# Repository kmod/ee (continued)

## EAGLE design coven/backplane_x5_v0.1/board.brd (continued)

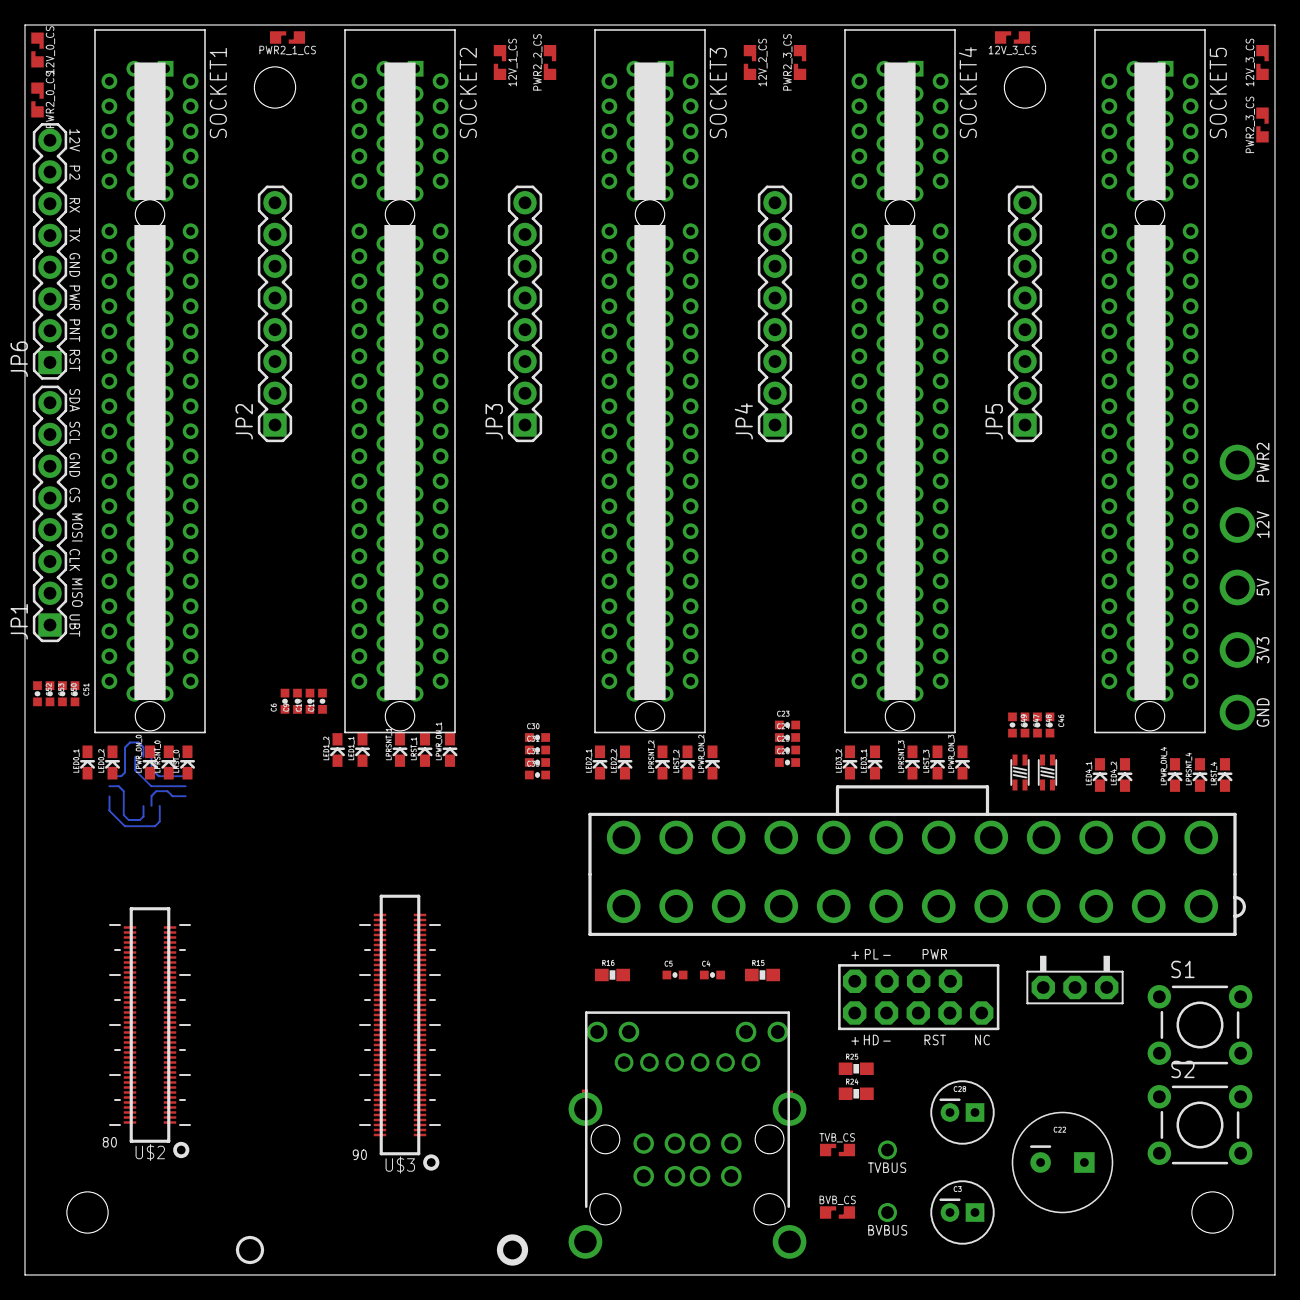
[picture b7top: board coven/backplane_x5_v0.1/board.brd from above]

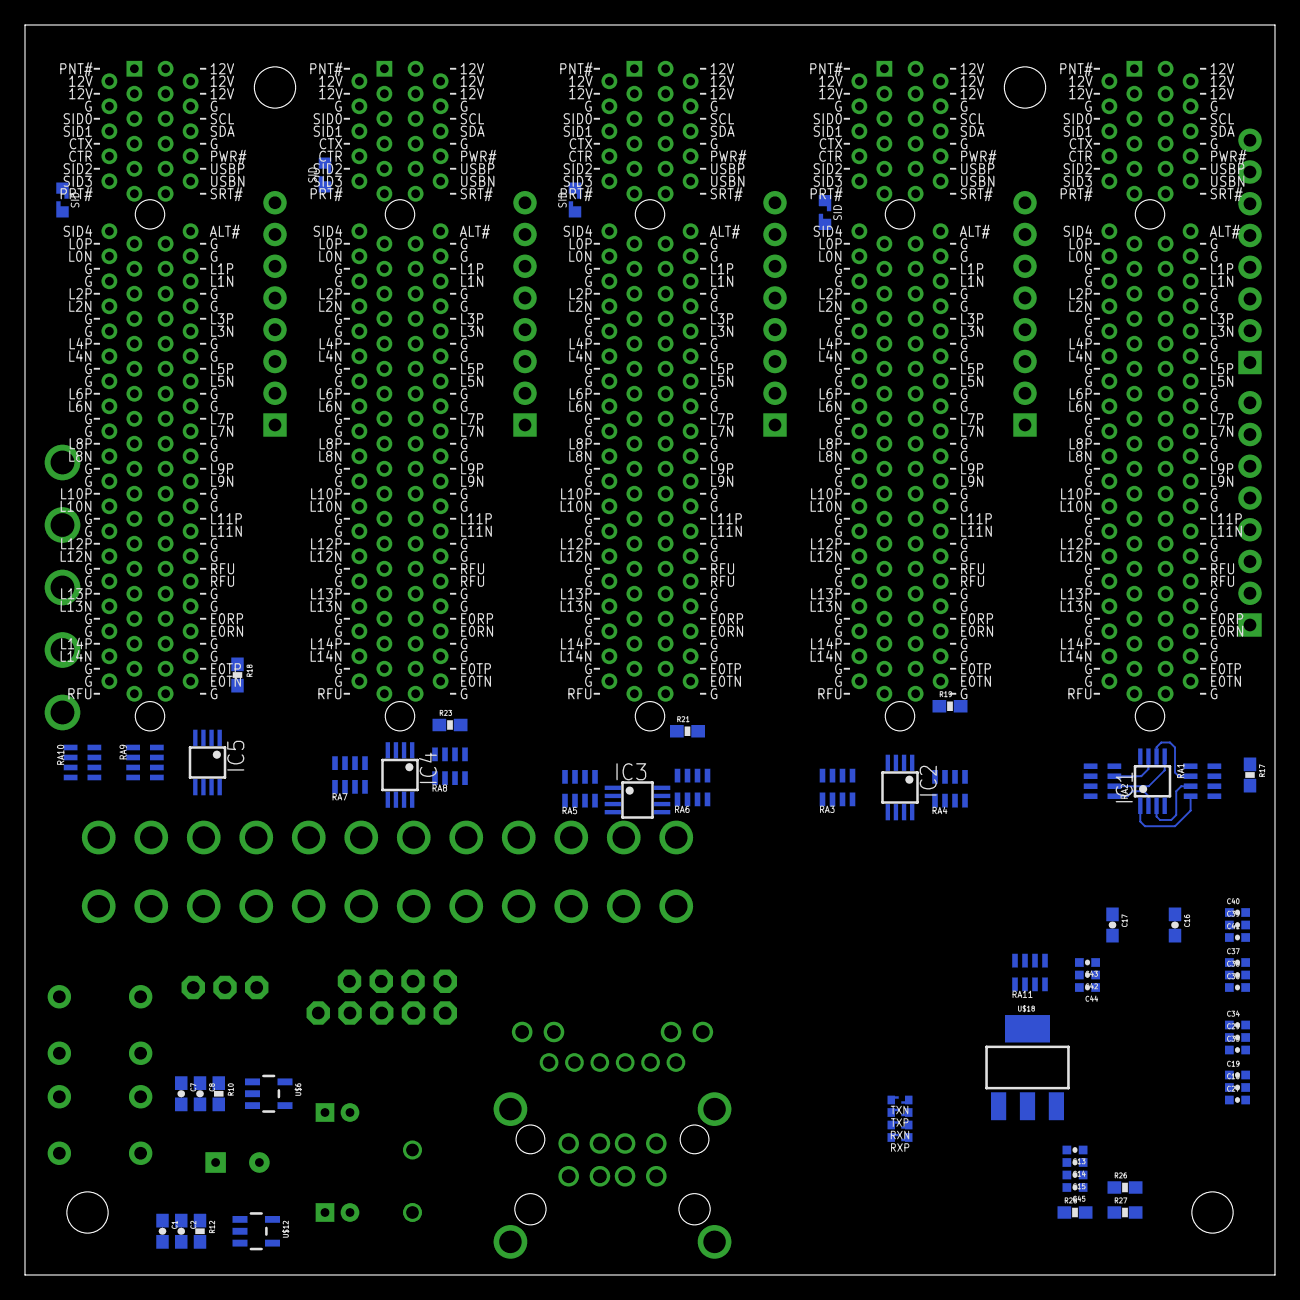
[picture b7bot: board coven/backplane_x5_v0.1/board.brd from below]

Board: 4 copper layers, 100.0 x 100.0 mm, 160 parts (62 on the bottom side), 206 nets.

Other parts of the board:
U$7, U$8, U$9, U$10: STAND-OFF

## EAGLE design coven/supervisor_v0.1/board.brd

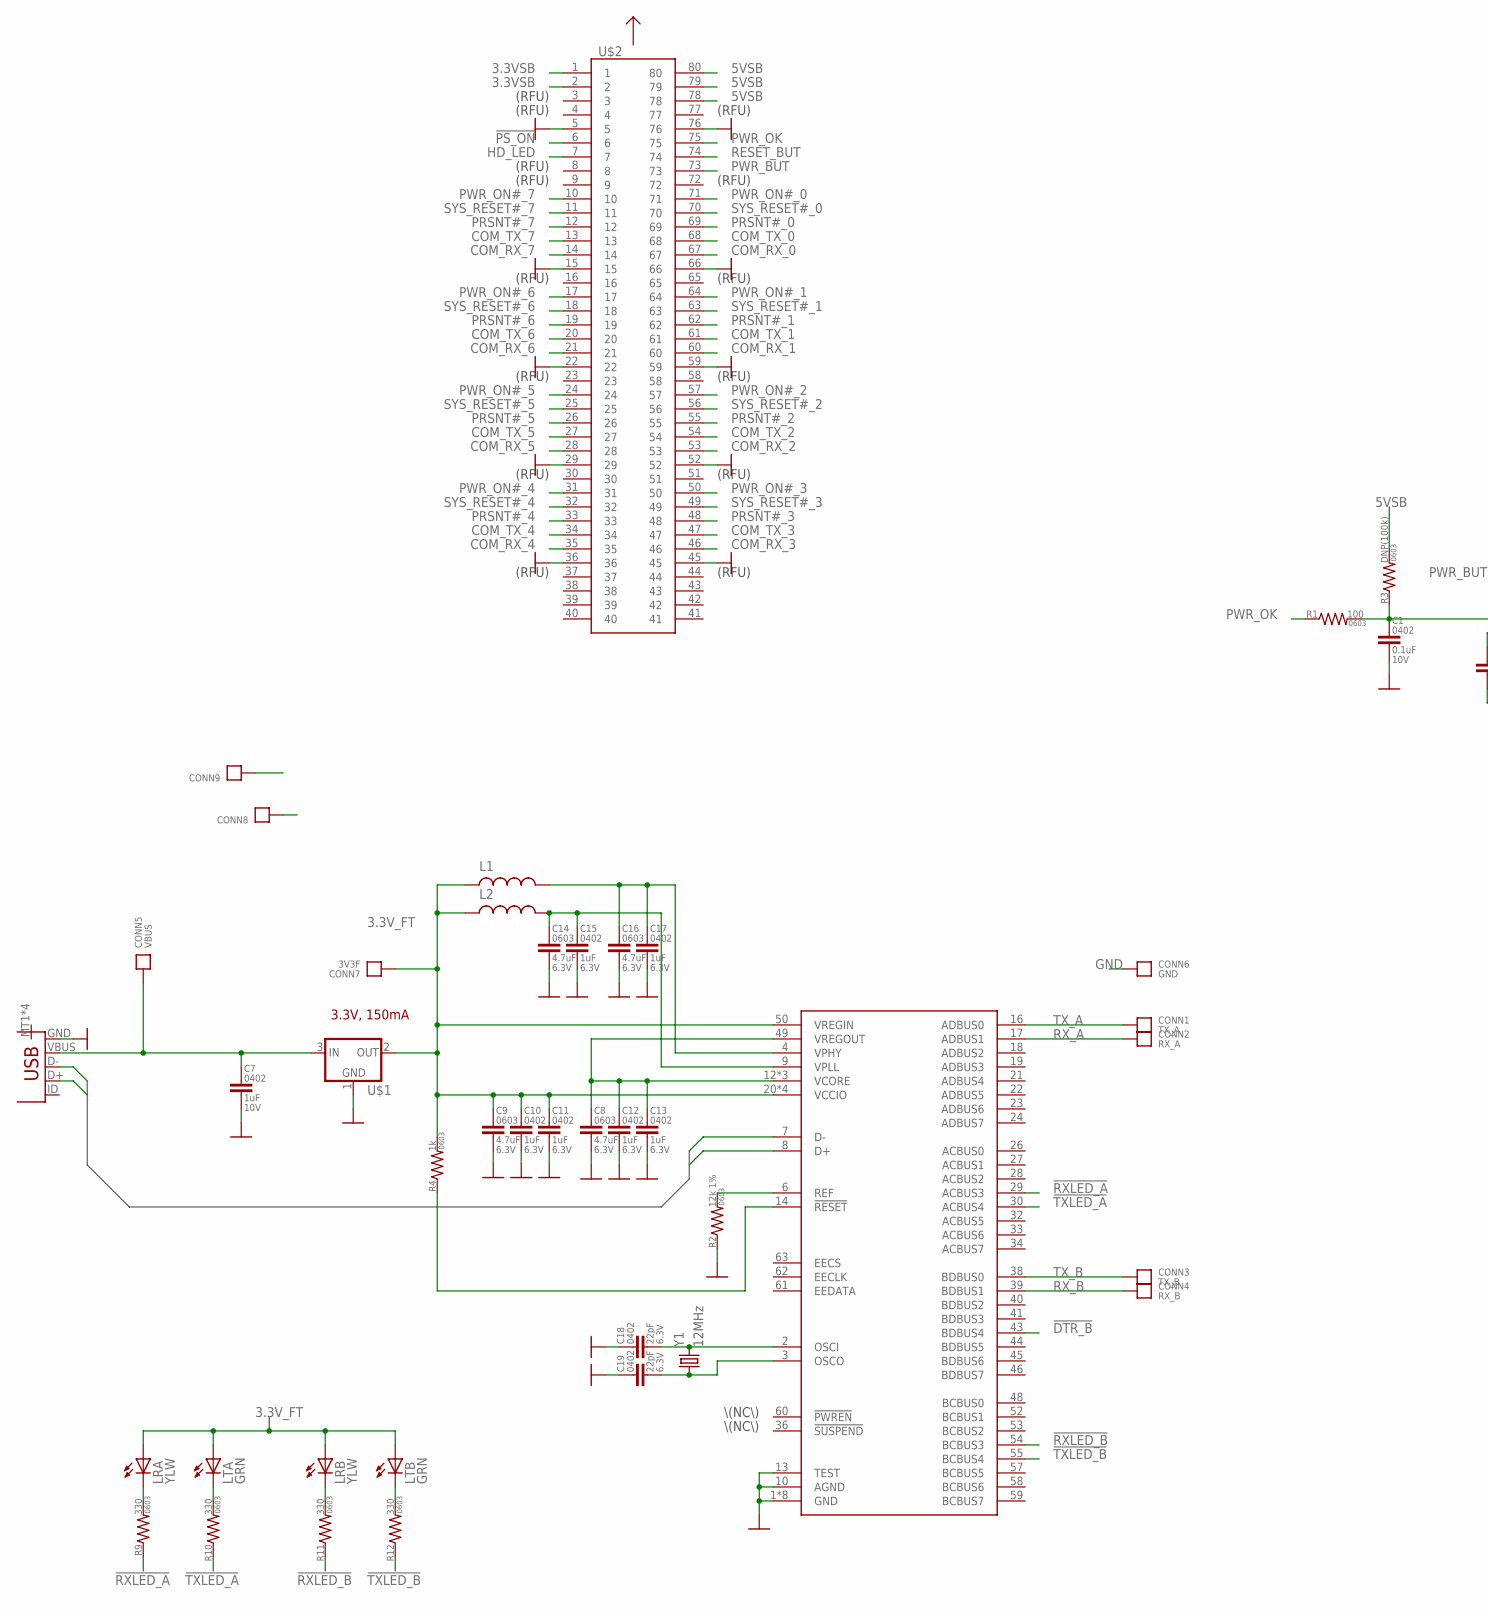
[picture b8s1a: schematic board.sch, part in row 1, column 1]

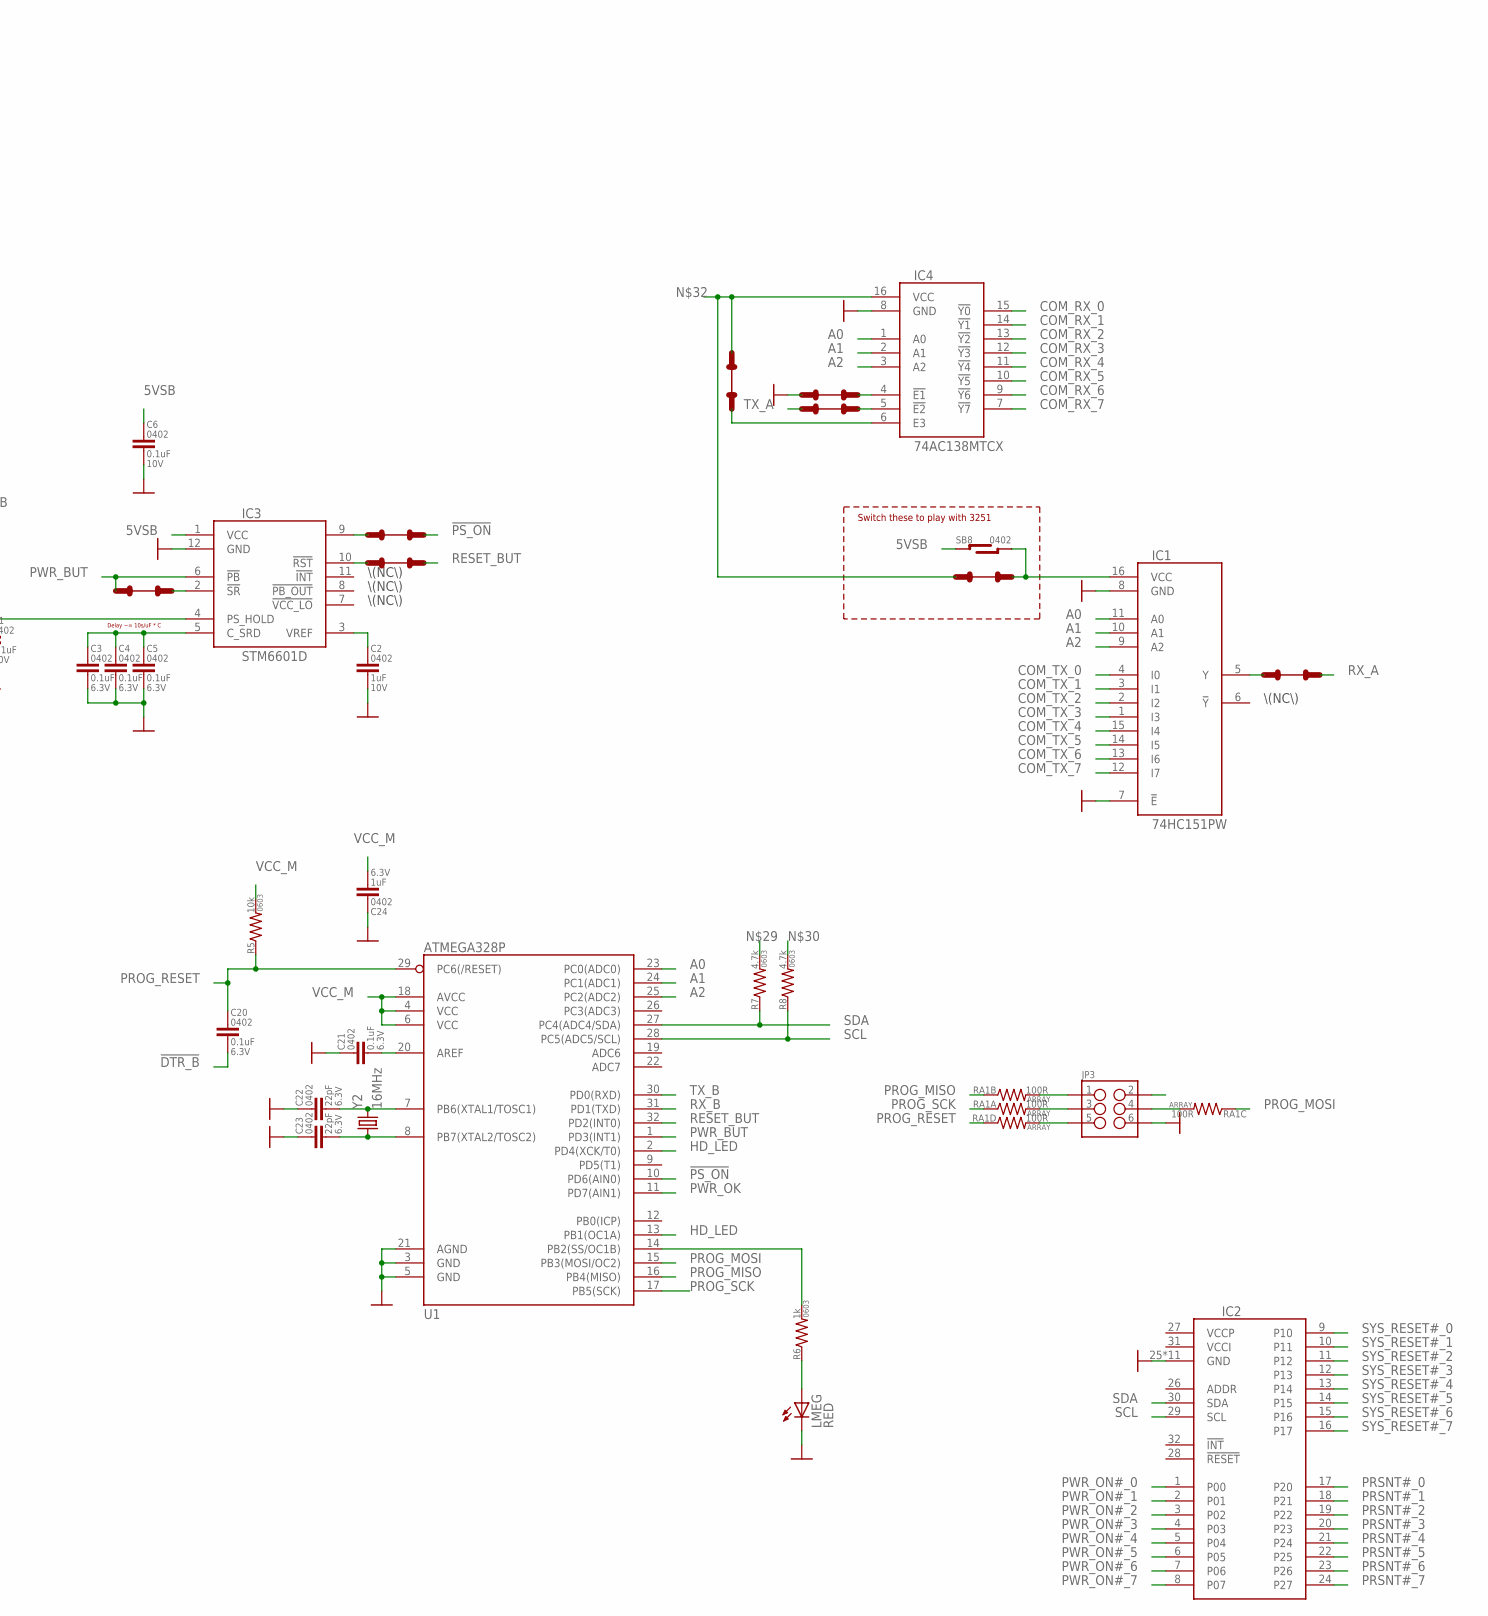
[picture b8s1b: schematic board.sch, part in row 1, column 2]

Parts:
C1, C6: 0.1uF; 0402-CAP; VOLTAGE 10V
C2, C7: 1uF; 0402-CAP; VOLTAGE 10V
C3, C4, C5, C20, C21: 0.1uF; 0402-CAP
C8, C9, C14, C16: 4.7uF; 0603-CAP
C10, C11, C12, C13, C15, C17, C24: 1uF; 0402-CAP
C18, C19, C22, C23: 22pF; 0402-CAP
CONN1: TX_A; HOLE_22AWG
CONN2: RX_A; HOLE_22AWG
CONN3: TX_B; HOLE_22AWG
CONN4: RX_B; HOLE_22AWG
CONN5: VBUS; HOLE_22AWG
CONN6: GND; HOLE_22AWG
CONN7: 3V3F; HOLE_22AWG
CONN8, CONN9: CONNECTOR22AWG; HOLE_22AWG
IC1: 74HC151PW; TSSOP16
IC2: TCA6424A; QFN32
IC3: STM6601D; TDFN12
IC4: 74AC138MTCX; TSSOP16
IC5: FT2232HL; TQFP64_LONGPAD
JP1: USB-IDMICRO; USB-MICRO
JP3: M03X2; 2X3_SMD
L1, L2: INDUCTOR0603; 0603
LMEG: RED; 0603_LED
LRA: YLW; 0603_LED
LRB: YLW; 0603_LED
LTA: GRN; 0603_LED
LTB: GRN; 0603_LED
R1: 100; 0603-RES
R2: 12k 1%; 0603-RES
R3: DNP(100k); 0603-RES
R4, R6: 1k; 0603-RES
R5: 10k; 0603-RES
R7, R8: 4.7k; 0603-RES
R9, R10, R11, R12: 330; 0603-RES
RA1: 100R; 0603-ARV
SB1, SB2, SB3, SB4, SB5, SB6, SB7, SB9: TRACE-CUT
SB8: SOLDER-BRIDGE0402; SB-0402
U1: ATMEGA328P; TQFP32-08
U$1: VREGSOT23-3; SOT23-3
U$2: DF40-80HDR; DF40-HDR-80
Y1: 12MHz; HC49UP
Y2: 16MHz; HC49UP

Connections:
3.3VSB: U$2.1, U$2.2
3.3V_FT: C9.1, C10.1, C11.1, CONN7.P, IC5.20 (VCCIO), IC5.31 (VCCIO), IC5.42 (VCCIO), IC5.50 (VREGIN), IC5.56 (VCCIO), L1.1, L2.1, LRA.A, LRB.A, LTA.A, LTB.A, R4.2, U$1.2 (OUT)
5VSB: C6.1, IC3.1 (VCC), R3.2, SB8.L1, SB8.L2, U$2.78, U$2.79, U$2.80
!DTR_B: C20.2, IC5.43 (BDBUS4)
!PS_ON: SB1.R1, U1.10 (PD6(AIN0)), U$2.6
!RXLED_A: IC5.29 (ACBUS3), R9.1
!RXLED_B: IC5.54 (BCBUS3), R11.1
!TXLED_A: IC5.30 (ACBUS4), R10.1
!TXLED_B: IC5.55 (BCBUS4), R12.1
A0: IC1.11 (A0), IC4.1 (A0), U1.23 (PC0(ADC0))
A1: IC1.10 (A1), IC4.2 (A1), U1.24 (PC1(ADC1))
A2: IC1.9 (A2), IC4.3 (A2), U1.25 (PC2(ADC2))
COM_RX_0: IC4.15 (!Y0), U$2.67
COM_RX_1: IC4.14 (!Y1), U$2.60
COM_RX_2: IC4.13 (!Y2), U$2.53
COM_RX_3: IC4.12 (!Y3), U$2.46
COM_RX_4: IC4.11 (!Y4), U$2.35
COM_RX_5: IC4.10 (!Y5), U$2.28
COM_RX_6: IC4.9 (!Y6), U$2.21
COM_RX_7: IC4.7 (!Y7), U$2.14
COM_TX_0: IC1.4 (I0), U$2.68
COM_TX_1: IC1.3 (I1), U$2.61
COM_TX_2: IC1.2 (I2), U$2.54
COM_TX_3: IC1.1 (I3), U$2.47
COM_TX_4: IC1.15 (I4), U$2.34
COM_TX_5: IC1.14 (I5), U$2.27
COM_TX_6: IC1.13 (I6), U$2.20
COM_TX_7: IC1.12 (I7), U$2.13
D+: IC5.8 (D+), JP1.D+
D-: IC5.7 (D-), JP1.D-
GND: C1.2, C2.2, C3.2, C4.2, C5.2, C6.2, C7.2, C8.2, C9.2, C10.2, C11.2, C12.2, C13.2, C14.2, C15.2, C16.2, C17.2, C18.1, C19.1, C21.1, C22.1, C23.1, C24.1, CONN6.P, IC1.7 (!E), IC1.8 (GND), IC2.25 (GND), IC2.PAD (GND), IC2.PAD1 (GND), IC2.PAD2 (GND), IC2.PAD3 (GND), IC2.PAD4 (GND), IC2.PAD5 (GND), IC2.PAD6 (GND), IC2.PAD7 (GND), IC2.PAD8 (GND), IC2.PAD9 (GND), IC3.12 (GND), IC4.8 (GND), IC5.1 (GND), IC5.5 (GND), IC5.10 (AGND), IC5.11 (GND), IC5.13 (TEST), IC5.15 (GND), IC5.25 (GND), IC5.35 (GND), IC5.47 (GND), IC5.51 (GND), JP1.GND, JP3.6, LMEG.C, R2.1, SB4.L1, U1.3 (GND), U1.5 (GND), U1.21 (AGND), U$1.1 (GND), U$2.5, U$2.15, U$2.22, U$2.29, U$2.36, U$2.45, U$2.52, U$2.59, U$2.66, U$2.76
HD_LED: U1.2 (PD4(XCK/T0)), U1.13 (PB1(OC1A)), U$2.7
unnamed: IC3.10 (!RST), SB3.L1
unnamed: C1.1, IC3.4 (PS_HOLD), R1.2, R3.1
unnamed: IC3.9 (EN/!EN), SB1.L1
unnamed: C2.1, IC3.3 (VREF)
unnamed: C3.1, C4.1, C5.1, IC3.5 (C_SRD)
unnamed: IC3.2 (!SR), SB2.R1
unnamed: C7.1, CONN5.P, JP1.VBUS, U$1.3 (IN)
unnamed: C14.1, C15.1, IC5.9 (VPLL), L2.2
unnamed: IC5.6 (REF), R2.2
unnamed: C8.1, C12.1, C13.1, IC5.12 (VCORE), IC5.37 (VCORE), IC5.49 (VREGOUT), IC5.64 (VCORE)
unnamed: C16.1, C17.1, IC5.4 (VPHY), L1.2
unnamed: IC5.14 (!RESET), R4.1
unnamed: C18.2, IC5.2 (OSCI), Y1.2
unnamed: C19.2, IC5.3 (OSCO), Y1.1
unnamed: C21.2, U1.20 (AREF)
unnamed: LRA.C, R9.2
unnamed: LTA.C, R10.2
unnamed: LRB.C, R11.2
unnamed: LTB.C, R12.2
unnamed: C22.2, U1.7 (PB6(XTAL1/TOSC1)), Y2.2
unnamed: C23.2, U1.8 (PB7(XTAL2/TOSC2)), Y2.1
unnamed: JP3.4, RA1.6 (2)
unnamed: IC4.6 (E3), SB5.L1
unnamed: JP3.5, RA1.5 (2)
unnamed: JP3.3, RA1.8 (2)
unnamed: JP3.1, RA1.7 (2)
unnamed: IC4.4 (!E1), SB4.R1
unnamed: IC4.16 (VCC), SB5.R1, SB9.L1
unnamed: IC4.5 (!E2), SB6.R1
unnamed: IC1.5 (Y), SB7.L1
unnamed: R6.2, U1.14 (PB2(SS/OC1B))
unnamed: LMEG.A, R6.1
unnamed: IC1.16 (VCC), SB8.R1, SB8.R2, SB9.R1
PROG_MISO: RA1.2 (1), U1.16 (PB4(MISO))
PROG_MOSI: RA1.3 (1), U1.15 (PB3(MOSI/OC2))
PROG_RESET: C20.1, R5.1, RA1.4 (1), U1.29 (PC6(/RESET))
PROG_SCK: RA1.1, U1.17 (PB5(SCK))
PRSNT#_0: IC2.17 (P20), U$2.69
PRSNT#_1: IC2.18 (P21), U$2.62
PRSNT#_2: IC2.19 (P22), U$2.55
PRSNT#_3: IC2.20 (P23), U$2.48
PRSNT#_4: IC2.21 (P24), U$2.33
PRSNT#_5: IC2.22 (P25), U$2.26
PRSNT#_6: IC2.23 (P26), U$2.19
PRSNT#_7: IC2.24 (P27), U$2.12
PWR_BUT: IC3.6 (!PB), SB2.L1, U1.1 (PD3(INT1)), U$2.73
PWR_OK: R1.1, U1.11 (PD7(AIN1)), U$2.75
PWR_ON#_0: IC2.1 (P00), U$2.71
PWR_ON#_1: IC2.2 (P01), U$2.64
PWR_ON#_2: IC2.3 (P02), U$2.57
PWR_ON#_3: IC2.4 (P03), U$2.50
PWR_ON#_4: IC2.5 (P04), U$2.31
PWR_ON#_5: IC2.6 (P05), U$2.24
PWR_ON#_6: IC2.7 (P06), U$2.17
PWR_ON#_7: IC2.8 (P07), U$2.10
RESET_BUT: SB3.R1, U1.32 (PD2(INT0)), U$2.74
RX_A: CONN2.P, IC5.17 (ADBUS1), SB7.R1
RX_B: CONN4.P, IC5.39 (BDBUS1), U1.31 (PD1(TXD))
SCL: IC2.29 (SCL), R8.1, U1.28 (PC5(ADC5/SCL))
SDA: IC2.30 (SDA), R7.1, U1.27 (PC4(ADC4/SDA))
SYS_RESET#_0: IC2.9 (P10), U$2.70
SYS_RESET#_1: IC2.10 (P11), U$2.63
SYS_RESET#_2: IC2.11 (P12), U$2.56
SYS_RESET#_3: IC2.12 (P13), U$2.49
SYS_RESET#_4: IC2.13 (P14), U$2.32
SYS_RESET#_5: IC2.14 (P15), U$2.25
SYS_RESET#_6: IC2.15 (P16), U$2.18
SYS_RESET#_7: IC2.16 (P17), U$2.11
TX_A: CONN1.P, IC5.16 (ADBUS0), SB6.L1
TX_B: CONN3.P, IC5.38 (BDBUS0), U1.30 (PD0(RXD))
VCC_M: C24.2, R5.2, U1.4 (VCC), U1.6 (VCC), U1.18 (AVCC)

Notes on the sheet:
Delay ~= 10s/uF * C
\(NC\)
3.3V, 150mA
Switch these to play with 3251
(RFU)

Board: 4 copper layers, 74 parts (1 on the bottom side), 103 nets, no tracks yet.

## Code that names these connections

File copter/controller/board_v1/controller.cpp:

#include "Arduino.h"

// PB1
#define LED0 9
// PB0
#define LED1 8
// PD7
#define LED2 7
// PD6
#define LED3 6

// PD2
#define SS0 2
// PD5
#define SS1 5
// PD4
#define SS2 4
// PD3
#define SS3 3

// PB3
#define MOSI 11
// PB4
#define MISO 12
// PB5
#define SCK 13
#define SS 10
void setup() {
    pinMode(LED0, OUTPUT);
    pinMode(LED1, OUTPUT);
    pinMode(LED2, OUTPUT);
    pinMode(LED3, OUTPUT);

    pinMode(SS0, OUTPUT);
    pinMode(SS1, OUTPUT);
    pinMode(SS2, OUTPUT);
    pinMode(SS2, OUTPUT);

    pinMode(MOSI, OUTPUT);
    pinMode(MISO, INPUT);
    pinMode(SCK, OUTPUT);

    // Activate the pullup on SS to make sure the SPI circuitry stays in master mode.
    // Alternatively, could set the pinMode to output
    pinMode(SS, INPUT);
    digitalWrite(SS, 1);

    SPCR = (1<<SPE) | (1<<MSTR) | (1<<SPR0) | (1<<CPHA);

    digitalWrite(SS1, 0);
    digitalWrite(LED3, 1);
    /*
    for (int i = 0; i < 64; i++) {
        SPDR = i;
        //while (!(SPSR & (1<<SPIF))) {
        while (!bitRead(SPSR, SPIF)) {
            digitalWrite(LED2, 1);
        }
        delay(100);
    }*/
    /*uint8_t c = SPDR;
    digitalWrite(LED0, (SPDR>>0)&1);
    digitalWrite(LED1, (SPDR>>1)&1);
    digitalWrite(LED2, (SPDR>>2)&1);
    digitalWrite(LED3, (SPDR>>3)&1);
    delay(2000);*/
    for (byte b = 180; b >= 80; b--) {
        SPDR = b;
        while (!bitRead(SPSR, SPIF));
        delay(200);
    }
    digitalWrite(SS1, 1);
    digitalWrite(LED3, 0);
    SPCR = 0;

    pinMode(MOSI, INPUT);
    pinMode(SCK, INPUT);
}

void loop() {
    digitalWrite(LED3, 0);
    digitalWrite(LED0, 1);
    delay(300);
    digitalWrite(LED0, 0);
    digitalWrite(LED1, 1);
    delay(300);
    digitalWrite(LED1, 0);
    digitalWrite(LED2, 1);
    delay(300);
    digitalWrite(LED2, 0);
    digitalWrite(LED3, 1);
    delay(300);
}
